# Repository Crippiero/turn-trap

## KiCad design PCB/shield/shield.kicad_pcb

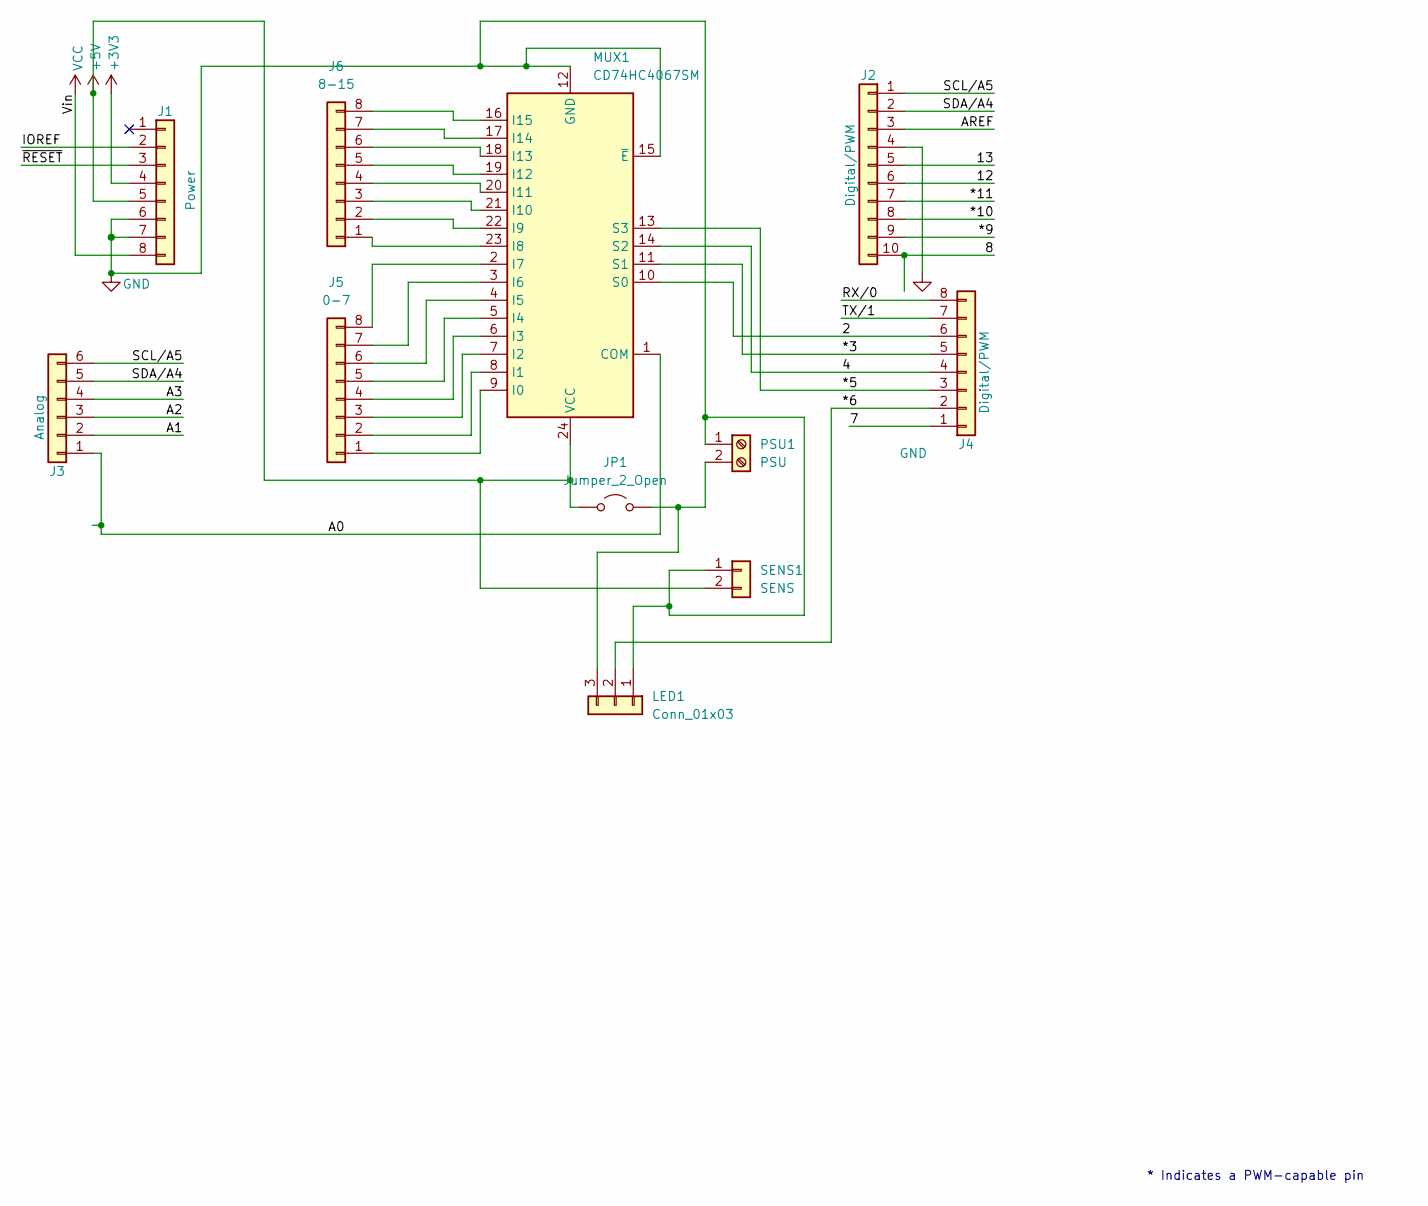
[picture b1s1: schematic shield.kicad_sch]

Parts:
J1: Power; PinSocket_1x08_P2.54mm_Vertical
J2: Digital/PWM; PinSocket_1x10_P2.54mm_Vertical
J3: Analog; PinSocket_1x06_P2.54mm_Vertical
J4: Digital/PWM; PinSocket_1x08_P2.54mm_Vertical
J5: 0-7; PinSocket_1x08_P2.54mm_Vertical
J6: 8-15; PinSocket_1x08_P2.54mm_Vertical
JP1: Jumper_2_Open; PinHeader_1x02_P2.54mm_Vertical
LED1: Conn_01x03; PinSocket_1x03_P2.54mm_Vertical
MUX1: CD74HC4067SM; SSOP-24_5.3x8.2mm_P0.65mm
PSU1: PSU; TerminalBlock_Phoenix_MKDS-1,5-2_1x02_P5.00mm_Horizontal
SENS1: SENS; PinSocket_1x02_P2.54mm_Vertical

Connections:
+3V3: J1.4
+5V: J1.5, JP1.1 (A), MUX1.24 (VCC), SENS1.2
/2: J4.6, MUX1.10 (S0)
/4: J4.4, MUX1.14 (S2)
/7: J4.1
/8: J2.10
/12: J2.6
/13: J2.5
/*3: J4.5, MUX1.11 (S1)
/*5: J4.3, MUX1.13 (S3)
/*6: J4.2, LED1.2
/*9: J2.9
/*10: J2.8
/*11: J2.7
/A0: J3.1, MUX1.1 (COM)
/A1: J3.2
/A2: J3.3
/A3: J3.4
/AREF: J2.3
/IOREF: J1.2
/RX/0: J4.8
/SCL/A5: J2.1, J3.6
/SDA/A4: J2.2, J3.5
/TX/1: J4.7
/~RESET: J1.3
GND: J1.6, J1.7, J2.4, LED1.1, MUX1.12 (GND), MUX1.15 (~E), PSU1.1, SENS1.1
unnamed: J5.1, MUX1.9 (I0)
unnamed: J5.2, MUX1.8 (I1)
unnamed: J5.3, MUX1.7 (I2)
unnamed: J5.4, MUX1.6 (I3)
unnamed: J5.5, MUX1.5 (I4)
unnamed: J5.6, MUX1.4 (I5)
unnamed: J5.7, MUX1.3 (I6)
unnamed: J5.8, MUX1.2 (I7)
unnamed: J6.1, MUX1.23 (I8)
unnamed: J6.2, MUX1.22 (I9)
unnamed: J6.3, MUX1.21 (I10)
unnamed: J6.4, MUX1.20 (I11)
unnamed: J6.5, MUX1.19 (I12)
unnamed: J6.6, MUX1.18 (I13)
unnamed: J6.7, MUX1.17 (I14)
unnamed: J6.8, MUX1.16 (I15)
unnamed: JP1.2 (B), LED1.3, PSU1.2
VCC: J1.8

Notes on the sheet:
* Indicates a PWM-capable pin

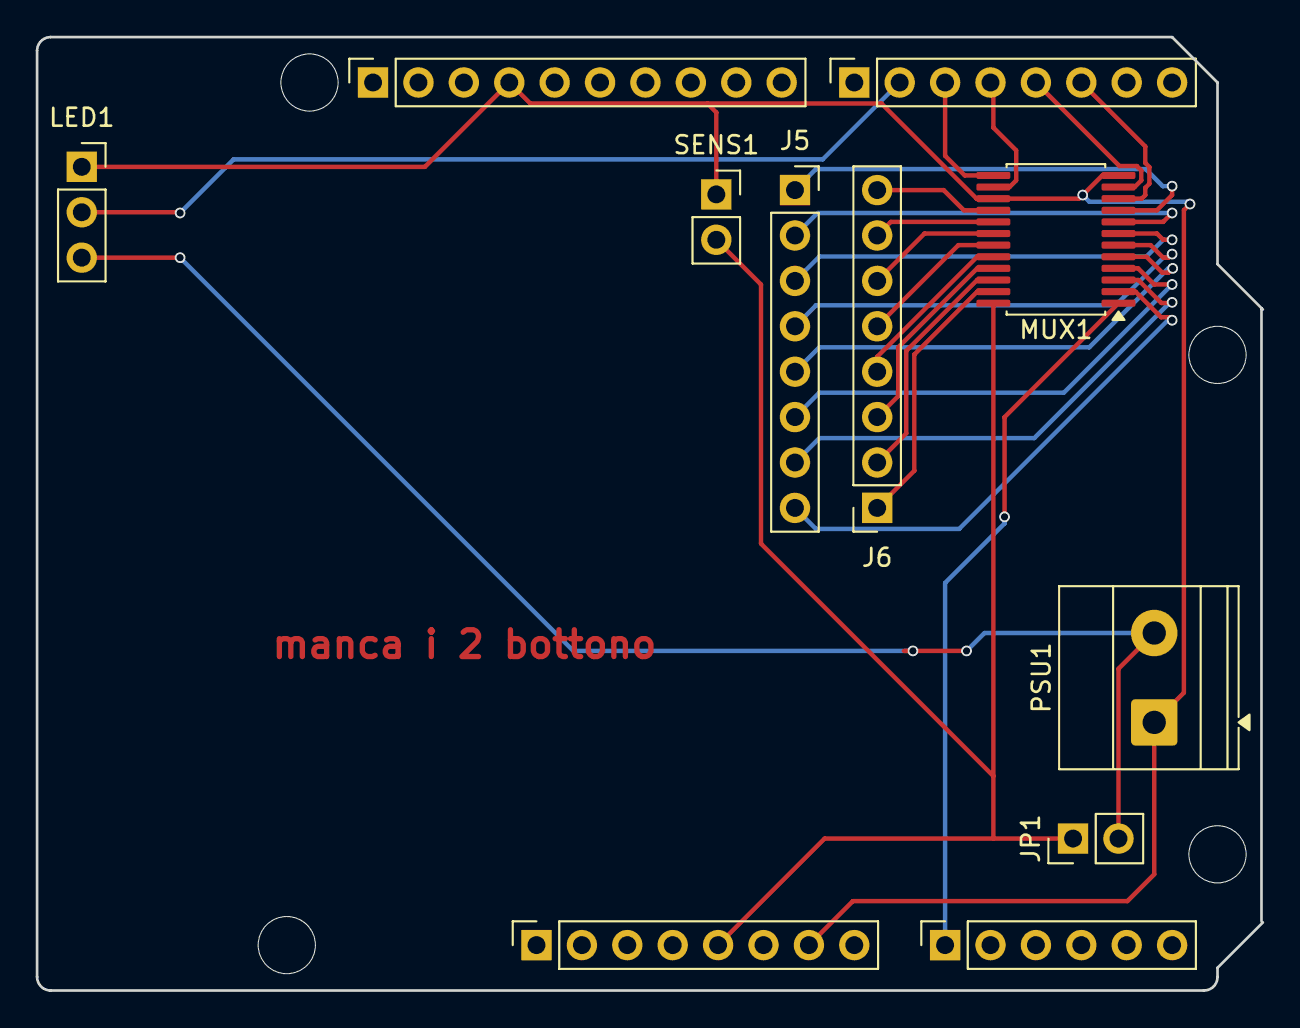
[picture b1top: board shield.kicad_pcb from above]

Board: 2 copper layers, 68.6 x 53.3 mm, 15 parts (0 on the bottom side), 27 nets.

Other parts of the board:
MH1, MH2, MH3, MH4: MountingHole_3.2mm

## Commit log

2026-03-18 Rename HallSensorsToLed.ino to HallSensorsToLed/HallSensorsToLed.ino
2026-03-31 Refine game rules and robot description in doc.tex
2026-03-31 Add NeoPixel control for two strips
2026-03-31 Rename 74HC4067.jpg to img/74HC4067.jpg
2026-03-31 Rename addressableLed.png to img/addressableLed.png
2026-03-31 Rename hall.png to img/hall.png
2026-03-31 Rename logo.png to img/logo.png
2026-03-31 Rename prototipo.jpg to img/prototipo.jpg
2026-03-31 Rename scacchiera.png to img/scacchiera.png
2026-03-31 Rename 2strisce-viola to 2-purple-stips/2-purple-strip.ino
2026-03-31 Rename prova-led-labirinto.ino to prova-led-labirinto/prova-led-labirinto.ino
2026-03-31 cambiamento stuttura file
2026-03-31 Rename doc.tex to documentazione/doc.tex
2026-04-01 Rename 2-purple-strip.ino to 2-purple-strip.ino
2026-04-01 Rename prova-led-labirinto.ino to prova-led-labirinto.ino
2026-04-01 Add labirinto5x5 for controlling NeoPixel strips
2026-04-01 Add RGB LED control for multiple strips
2026-04-04 Update labirinto5x5
2026-04-08 Create switch-labirinto-5x5
2026-04-08 Add segmented lighting control for NeoPixel strips
2026-04-08 Rename code/prova-led/2-purple-strip.ino to code/prova-led/2-purple-strip/2-purple-strip.ino
2026-04-08 Rename code/prova-led/prova-led-labirinto.ino to code/prova-led/prova-led-labirinto/prova-led-labirinto.ino
2026-04-08 Rename scacchi-rosso-viola to scacchi-rosso-viola.ino
2026-04-08 Rename code/prova-led/scacchi-rosso-viola.ino to code/prova-led/scacchi-rosso-viola/scacchi-rosso-viola.ino
2026-04-08 Rename labirinto5x5 to labirinto5x5.ino
2026-04-08 Rename code/prova-led/labirinto5x5.ino to code/prova-led/labirinto5x5/labirinto5x5.ino
2026-04-08 Rename switch-labirinto-5x5 to switch-labirinto-5x5.ino
2026-04-08 Rename code/prova-led/switch-labirinto-5x5.ino to code/prova-led/switch-labirinto-5x5/switch-labirinto-5x5.ino
2026-04-08 Create multiplexerRegistri
2026-04-08 Update multiplexerRegistri
2026-04-09 Create DFSonStrip
2026-04-09 Rename DFSonStrip to DFconStrip.ino
2026-04-09 Change Podium coordinates to int8_t and update logic
    Changed data type of x and y in Podium structure from uint8_t to int8_t. Updated initialization in magnetDetection function and adjusted condition in debug print statement.
2026-04-16 Riorganizzazione file
2026-04-29 creazione nuovi file
2026-04-29 modifiche pin
2026-04-29 removed old pin for button
2026-04-29 utilizzo di constexpr per un boot piu veloce
2026-04-29 aggiunta della lettura da seriale
2026-04-29 modifiche ad alcune costanti e generazione del labirinto su pagina web
2026-04-29 correzione logica posizione giocatori
2026-04-30 removed ghost file
2026-04-30 Prova
2026-04-30 annulla prova
2026-04-30 added color variable
2026-04-30 Color
2026-04-30 maiusc
2026-04-30 addedd the function addOpenBorders()
2026-05-01 fn generateUnprPoint
2026-05-01 uint8 to point in generateUnprPoint
2026-05-01 Add Arduino sketch for NeoPixel control
2026-05-01 Set LED strip brightness to 100
2026-05-01 finie di generateUnprPoint
2026-05-06 linea 225 int to uint
2026-05-06 if to switch line 256
2026-05-06 aggiunta di nuove funzioni
2026-05-06 Rimosso un duplicato di chiamata della funzione renderNewMaze in riga 455
2026-05-06 stampa su seriale mentre si aspetta per il reset
2026-05-06 Separation of Concernen del void loop, creando processSerialCommands()
2026-05-06 Creo un punto per salvare unpr. Correzione errori di compilazione dovuti a ";" mancanti. Aggiunto un limite alle prove nella funzione generateUnprPoint per evitare loop infiniti. Modifica di resoluti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
2026-05-06 Uso di millis() al posto di delay per non far addormentare l'arduino
2026-05-06 correzione sintassi
2026-05-06 Cambio della variabile try a Gentry perchè try non valido
2026-05-07 aggiunta di getPixelIndex non ancora implementata
2026-05-07 Aggiornamento printUnpr e inizio di checkUnpr
2026-05-07 Prima versione della funzione checkUnpr.
2026-05-07 inizio del primo caso
2026-05-07 implementazione di getPixelIndex in renderNewMaze
2026-05-07 correzione logica
2026-05-07 semplificazione di getUnpr con implementazione del doppio turno
2026-05-07 prima versione finita di getUnpr
2026-05-07 correzioni per errori di compilazione
2026-05-07 miglioramento di getUnpr
2026-05-07 ulteriore miglioramento di getUnpr
2026-05-07 Modifica a getUnpr con rimozione del colore dopo 1 secondo
2026-05-07 aggiunta strip.show per visualizzare le modifiche di unpr
2026-05-07 Piccole migliorie e da Gentry a genTry
2026-05-07 spostamento di unpr dal loop alla funzione processSerialCommands
2026-05-08 creazione di nuovi file per la gestione dei led con un'arduino a parte
2026-05-08 Copia di Esp.ino dalla cartella conEspWifi a EspWifi-LedDriver
2026-05-08 prime funzioni nel nuovo file
2026-05-09 aggiunta codice per master modificato
2026-05-09 aggiunta supporto esp e slave
2026-05-09 modifica di slave.ino per dividere le strisce
2026-05-09 inversione a serpentina nello slave
2026-05-09 reintroduzione di resolutuion
2026-05-09 rinominata la funzione isValidinUnpr in inGame
2026-05-09 correzioni di layout
2026-05-09 correzione layout
2026-05-09 correzione processCommand e correzione layout
2026-05-09 correzione di getUnpr per gestire il turno bloccato di un giocatore
2026-05-09 correzione ultima parte del layout
2026-05-09 modifiche di variabile in slave.ino
2026-05-09 aggiunta di funzioni per comunicare al web cosa sta facendo il master con parole testuali
2026-05-09 implementazione di SendInfoToWeb in ResetCalibration
2026-05-09 miglioramento esp.ino
2026-05-09 modalità accesPoint invede di host
2026-05-09 correzione di una funzione fantasma rimasta dopo il cambio del nome
2026-05-09 nuova versione di eso.ino non testata
2026-05-10 RItorno al file corretto
2026-05-10 creazione di NeopixelFake per non dover riscrivere l'intero codice
2026-05-10 codici FUNZIONANTI
2026-05-10 ulteriori modifiche per il miglioramento del sito web
2026-05-10 modifiche funzionanti tranne i popup
